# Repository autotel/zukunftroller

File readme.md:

#Building Controller shematic
##Pin allocation

Inputs/ outputs requeridos
```
                                1: 25 botones en circulo
                                  |  2: 11 botones de modo
                                  |  |  3: 2 terminales de led independientes
                                  |  |  |  4: 11 terminales independientes de led
                                  |  |  |  |  5: 3 terminales para controlar dos pantallas (clock,data,?)
                                  |  |  |  |  |  6: 12 encoder 12 estados
                                  |  |  |  |  |  |  7: 1 botón reset (usaremos el pin reset de arduino)
                                  |  |  |  |  |  |  |  8: 4 dos encoders de parámetro
                                  |  |  |  |  |  |  |  |  9: 2 pines display oLed sobre I2C
                                  |  |  |  |  |  |  |  |  |  10: 1 Midi out
                                  |  |  |  |  |  |  |  |  |  |  11: 1 Midi o serial in (para acoplar teclado melódico, que es un desarrollo aparte)
Pines de los multiplexores -------|--|--|--|--|--|--|--|--|--|--| --------------------------------------------------------------------------
                                  |  |  |  |  |  |  |  |  |  |  |  12: 8 MUX address
                                  |  |  |  |  |  |  |  |  |  |  |  |  13: 2 MUX Common
                                  |  |  |  |  |  |  |  |  |  |  |  |  |  14: 3 Shift register
... van conectados al pin...------|--|--|--|--|--|--|--|--|--|--|--|--|--|---------------------------------------------------------------------
                                  |  |  |  |  |  |  |  |  |  |  |  |  |  |    Total usado:
Directo arduino (18,+1 Tx)--------|--|--|--|--|--|--|--|--|--|--|--| 8| 2|--  | 10/18
Terminal Reset (1)----------------|--|--|--|--|--|--| 1|--|--|--|--|--|--|--  | 1/1
Multiplexor Directo (n=32)--------|--|--|--|--| 3|--|--| 4| 2| 1|--|--|--| 3  | 13/32
Multiplexor en Matrix (256-n^2)---|25|11|--|--|--|12|--|--|--|--|--|--|--|--  | 48/(256-13^2)
Puerto serial in Arduino (1)------|--|--|--|--|--|--|--|--|--|--| 1|--|--|--  | 1/1
Shift register (8 o 16)-----------|--|--| 2|11|--|--|--|--|--|--|--|--|--|--  | 13/16
```

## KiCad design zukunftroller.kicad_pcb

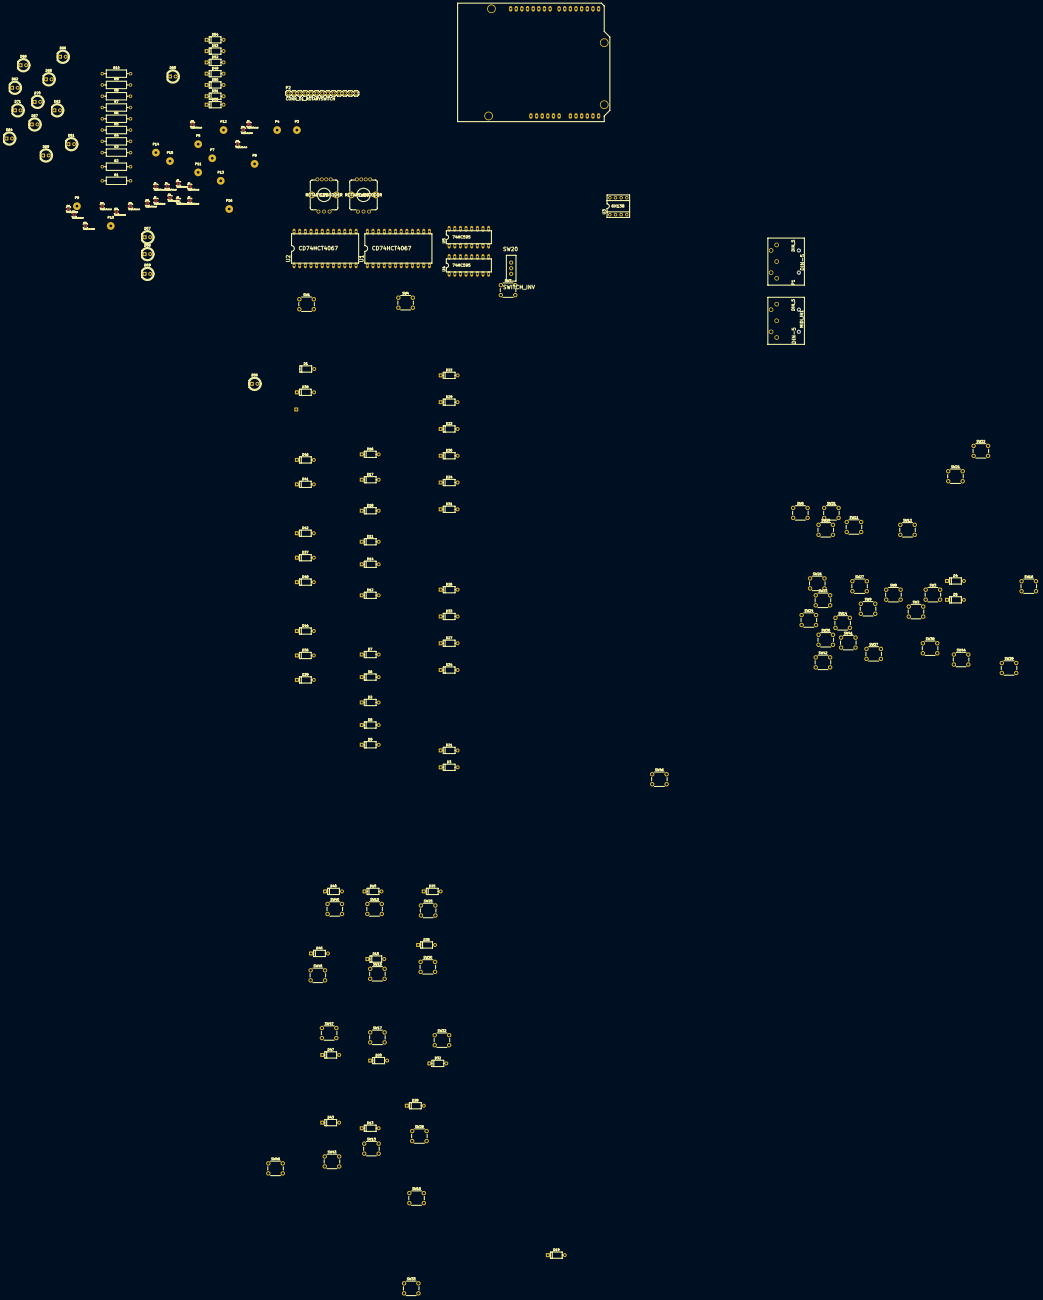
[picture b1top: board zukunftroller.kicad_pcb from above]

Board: 2 copper layers, 168 parts (0 on the bottom side), 129 nets, no tracks yet.

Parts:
D1, D2, D3, D4, D5, D6, D7, D8, D9, D10, D11, D12, D13, D14, D15, D16, D17, D18, D19, D20, D21, D22, D23, D24, D25, D26, D27, D28, D29, D30, D31, D32, D33, D34, D35, D36, D37, D38, D39, D40, D41, D42, D43, D44, D45, D46, D47, D48, D49, D50, D51, D52, D53, D54, D55: D; D_A-405_P7.62mm_Horizontal
D56, D57, D58, D59, D60, D61, D62, D63, D64, D65, D66, D67, D68, D69, D70, D71: LED; LED_D5.0mm
JP1, JP2, JP3, JP4, JP5, JP6, JP7, JP8, JP9, JP10, JP11, JP12, JP13, JP14, JP15, JP16, JP17, JP18, JP19: Jumper_NO_Small; PAD-JUMPER-2-NO_YES_SILK
MIDI_IN1: DIN_5; DIN_5_FEMALE
P1: DIN_5; DIN_5_FEMALE
P2: CONN_01_ROTARYSWITCH; 1X13
P3, P4, P5, P7, P8, P9, P10, P11, P12: CONN_01X01; SolderWirePad_single_1-2mmDrill
P13, P14: CONN_01X05; SolderWirePad_single_1-2mmDrill
P15: CONN_01X08; SolderWirePad_single_1-2mmDrill
P16: CONN_02X03; SolderWirePad_single_1-2mmDrill
R1, R2, R3, R4, R5, R6, R7, R8, R9, R10: R; R_Axial_DIN0309_L9.0mm_D3.2mm_P12.70mm_Horizontal
SHIELD1: ARDUINO_SHIELD; ARDUINO SHIELD
SW1, SW2, SW3, SW4, SW6, SW7, SW8, SW9, SW10, SW11, SW12, SW13, SW14, SW15, SW16, SW17, SW18, SW21, SW22, SW23, SW24, SW25, SW26, SW27, SW28, SW29, SW30, SW31, SW32, SW33, SW36, SW37, SW38, SW39, SW40, SW41, SW42, SW43, SW44, SW45, SW46, SW47, SW48: SW_PUSH; SW_PUSH_6mm
SW5, SW19: ROTARY_ENCODER; ENCODER_LED_2
SW20: SWITCH_INV; SWITCH-SPDT
U1, U2: CD74HCT4067; DIL24-6
U3: 6N138; DIL08
U4, U5: 74HC595; DIL16

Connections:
/CLK: JP10.2, JP11.2
/MUXACOM: R1.1, SHIELD1.AD0, U1.1
/MUXA_ADDR0: SHIELD1.4, U1.10
/MUXA_ADDR1: SHIELD1.5, U1.11
/MUXA_ADDR2: SHIELD1.6, U1.14
/MUXA_ADDR3: SHIELD1.7, U1.13
/MUXA_CONN_0: D5.1, SW1.1, SW2.1, SW3.1, U1.9
/MUXA_CONN_1: D19.1, SW18.1, SW33.1, SW48.1, U1.8
/MUXA_CONN_2: D20.1, SW17.1, SW32.1, SW47.1, U1.7
/MUXA_CONN_3: D34.1, SW16.1, SW31.1, SW46.1, U1.6
/MUXA_CONN_4: D35.1, SW15.1, SW30.1, SW45.1, U1.5
/MUXA_CONN_5: D49.1, SW14.1, SW29.1, SW44.1, U1.4
/MUXA_CONN_6: D50.1, SW13.1, SW28.1, SW43.1, U1.3
/MUXA_CONN_7: D51.1, SW12.1, SW27.1, SW42.1, U1.2
/MUXA_CONN_8: D52.1, SW11.1, SW26.1, SW41.1, U1.23
/MUXA_CONN_9: D53.1, SW10.1, SW25.1, SW40.1, U1.22
/MUXA_CONN_A: D54.1, SW9.1, SW24.1, SW39.1, U1.21
/MUXA_CONN_B: D55.1, SW8.1, SW23.1, SW38.1, U1.20
/MUXA_CONN_C: SW7.1, SW22.1, SW37.1, U1.19
/MUXA_CONN_D: SW6.1, SW21.1, SW36.1, U1.18
/MUXA_CONN_E: U1.17, U4.11, U4.12
/MUXA_CONN_F: JP5.1, JP10.1, JP16.1, P12.1, U1.16
/MUXBCOM: R2.1, SHIELD1.AD1, U2.1
/MUXB_ADDR0: SHIELD1.8, U2.10
/MUXB_ADDR1: SHIELD1.9, U2.11
/MUXB_ADDR2: SHIELD1.10, U2.14
/MUXB_ADDR3: SHIELD1.11, U2.13
/MUXB_CONN_0: D1.1, D36.1, D37.1, D38.1, D39.1, D40.1, D41.1, D42.1, D43.1, D44.1, D45.1, D46.1, D47.1, D48.1, U2.9
/MUXB_CONN_1: D3.1, D21.1, D22.1, D23.1, D24.1, D25.1, D26.1, D27.1, D28.1, D29.1, D30.1, D31.1, D32.1, D33.1, U2.8
/MUXB_CONN_2: D2.1, D6.1, D7.1, D8.1, D9.1, D10.1, D11.1, D12.1, D13.1, D14.1, D15.1, D16.1, D17.1, D18.1, U2.7
/MUXB_CONN_3: P2.1, U2.6
/MUXB_CONN_4: P1.5, U2.5
/MUXB_CONN_5: U2.4, U5.11, U5.12
/MUXB_CONN_6: JP3.1, JP8.1, U2.3
/MUXB_CONN_7: JP4.1, R8.2, SW20.1, U2.2
/MUXB_CONN_8: JP15.1, P8.1, U2.23
/MUXB_CONN_D: P16.1, U2.18
/PD0: R6.2, SHIELD1.0, U3.6
/PD2: SHIELD1.2, U4.13, U5.13
/RESET: SHIELD1.RST, SW4.1
/SSEL_1: JP9.1, R9.1, SW20.3
GND: JP2.1, JP7.1, JP13.1, JP17.1, P1.2, P11.1, R1.2, R2.2, R5.2, R7.1, R10.1, SHIELD1.GND3, SW4.2, SW20.2, U1.15, U2.15, U3.5, U4.8, U4.10, U5.8, U5.10
unnamed: D1.2, SW1.2
unnamed: D2.2, SW2.2
unnamed: D3.2, SW3.2
unnamed: D4.1, R4.1, U3.2
unnamed: D4.2, MIDI_IN1.5, U3.3
unnamed: D5.2, P2.2
unnamed: D6.2, SW6.2
unnamed: D7.2, SW7.2
unnamed: D8.2, SW8.2
unnamed: D9.2, SW9.2
unnamed: D10.2, SW10.2
unnamed: D11.2, SW11.2
unnamed: D12.2, SW12.2
unnamed: D13.2, SW13.2
unnamed: D14.2, SW14.2
unnamed: D15.2, SW15.2
unnamed: D16.2, SW16.2
unnamed: D17.2, SW17.2
unnamed: D18.2, SW18.2
unnamed: D19.2, P2.3
unnamed: D20.2, P2.4
unnamed: D21.2, SW21.2
unnamed: D22.2, SW22.2
unnamed: D23.2, SW23.2
unnamed: D24.2, SW24.2
unnamed: D25.2, SW25.2
unnamed: D26.2, SW26.2
unnamed: D27.2, SW27.2
unnamed: D28.2, SW28.2
unnamed: D29.2, SW29.2
unnamed: D30.2, SW30.2
unnamed: D31.2, SW31.2
unnamed: D32.2, SW32.2
unnamed: D33.2, SW33.2
unnamed: D34.2, P2.5
unnamed: D35.2, P2.6
unnamed: D36.2, SW36.2
unnamed: D37.2, SW37.2
unnamed: D38.2, SW38.2
unnamed: D39.2, SW39.2
unnamed: D40.2, SW40.2
unnamed: D41.2, SW41.2
unnamed: D42.2, SW42.2
unnamed: D43.2, SW43.2
unnamed: D44.2, SW44.2
unnamed: D45.2, SW45.2
unnamed: D46.2, SW46.2
unnamed: D47.2, SW47.2
unnamed: D48.2, SW48.2
unnamed: D49.2, P2.7
unnamed: D50.2, P2.8
unnamed: D51.2, P2.9
unnamed: D52.2, P2.10
unnamed: D53.2, P2.11
unnamed: D54.2, P2.12
unnamed: D55.2, P2.13
unnamed: D56.1, D57.1, D58.1, D59.1, D60.1, D61.1, D62.1, D63.1, R7.2
unnamed: D56.2, U4.15
unnamed: D57.2, U4.1
unnamed: D58.2, U4.2
unnamed: D59.2, U4.3
unnamed: D60.2, U4.4
unnamed: D61.2, U4.5
unnamed: D62.2, U4.6
unnamed: D63.2, U4.7
unnamed: D64.1, D65.1, D66.1, D67.1, D68.1, D69.1, D70.1, D71.1, R10.2
unnamed: D64.2, U5.15
unnamed: D65.2, U5.1
unnamed: D66.2, U5.2
unnamed: D67.2, U5.3
unnamed: D68.2, U5.4
unnamed: D69.2, U5.5
unnamed: D70.2, U5.6
unnamed: D71.2, U5.7
unnamed: JP1.2, P13.1
unnamed: JP12.2, P15.1
unnamed: JP14.1, P10.1
unnamed: JP18.1, P9.1
unnamed: JP19.1, P7.1
unnamed: MIDI_IN1.4, R4.2
unnamed: P1.4, R3.1
unnamed: P3.1, SHIELD1.GND1
unnamed: P4.1, SHIELD1.GND2
unnamed: P5.1, SHIELD1.V_IN
unnamed: R5.1, U3.7
unnamed: U4.9, U5.14
VCC: JP1.1, JP6.1, JP12.1, R3.2, R6.1, R8.1, R9.2, SHIELD1.5V, U3.8, U4.16, U5.16

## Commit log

2017-04-27 start creating shcematic
2017-04-27 name mux output and create button block
2017-04-27 array of buttons in blocks
2017-04-27 planned pin allocation
2017-04-27 button matrix
2017-04-27 -changes in pin allocation -most of the wiring
2017-04-27 rename readme
2017-04-27 readme correction
2017-04-27 don't seem to get the md right :S
2017-04-27 fixed some wrong pin connections
2017-04-27 fixed a couple more of wrong pins & additional notes
2017-04-27 mux inhibit to ground
2017-04-27 comment: example code (not tested)
2017-04-28 added jumpers in case of error
2017-04-28 pins for vacant mux connections
2017-04-28 pull down resistors in mux commons
2017-04-28 resistor for leds in shoft register
2017-04-28 assigned footprints, in process of scattering elements in pcb
2017-04-28 sorting buttons, changed footprint of 4067
2017-04-28 more sorting
2017-04-28 pdf varsion of schamatic
